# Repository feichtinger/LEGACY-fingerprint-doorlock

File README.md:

# Fingerprint Doorlock
## Overview
A simple electronic doorlock using a fingerprint sensor. 

This project uses a ZFM-20 series fingerprint sensor to implement access controll (to a building or room) using an electrical doorlock (e.g. magnetic door buzzer).

All fingerprints can be managed by a simple GUI called Fingerprint-Manager or simply over a serial terminal.

## Features
* easy access without a key, card or code (cannot be lost or forgotten)
* up to 1000 fingers can be enrolled
* whole day access option (keep the door open during events etc.)
* easy administration using the Fingerprint-Manager
* logfiles about every access (optional)

## Bill of materials
* EVK1101 Eval-Board from Atmel (a different board with an AVR32 controller might work as well)
* a ZFM-20 series fingerprint sensor e.g.
[from ebay](http://www.ebay.at/itm/Optical-Finger-print-Reader-Fingerprint-Sensor-Module-for-Arduino-Locks-/121298397934?pt=UK_BOI_Industrial_Automation_Control_ET&hash=item1c3df2aaee)
* magnetic door buzzer (I took this one [from Reichelt](http://www.reichelt.de/T-R-FFNER-1B/3/index.html?&ACTION=3&LA=446&ARTICLE=58353&artnr=T%C3%9CR%C3%96FFNER+1B&SEARCH=T%C3%83%C2%BCr%C3%83%C2%B6ffner+1B))
* power supply 9VDC, 1.5A (e.g. [from Reichelt](http://www.reichelt.de/Festspannungsnetzteile/SNT-2250-9V/3/index.html?&ACTION=3&LA=2&ARTICLE=111183&GROUPID=4946&artnr=SNT+2250+9V))
* a SD-card for the EVK1101 (capacity does not matter)
* a distribution box for the controller board
* some installation material (cables, cable channel, screws ...)
* some electronic parts from the junk box (transistor, diode, resistor, veroboard,...)

optional:

* a realtime clock module (for logfiles)
* a weather-proof button (for whole day access)

## System Components
### Fingerprintsensor
The ZFM sensor is placed in a custom housing which can easily be produced using an 3D printer (and a little bit of manual work). The housing also includes a red and a green LED and optionally a button for whole day access (see below).

The sensor should be placed on the outside next to the door and is connected to the controller board with a 7-pole cable (you can use a piece of ethernet cable for this).

### Controller Board
The controller consists of the EVK1101 and some additional electronics:

* a little PWM step down circuit (transistor + diode) to drive the buzzer
* connectors for fingerprintsensor and buzzer
* a USB to serial converter

Of course the controller board needs to be placed **behind** the door in a closed housing (you can use an distribution box for this).

The 9V power supply is directly connected to the EVK1101. Be carefull to choose a power supply that privides enough current for the buzzer. This might also be temperature dependent so better measure the buzzer current at 9V and choose a bigger power supply to be on the save side. 1.5A fits for my buzzer.

### Magnetic Door Buzzer
The buzzer only releases the falling latch, so the lock bar always has to be pulled back.

The buzzer might get warm when it is activated for a longer period of time (especially when using the whole day access). The firmware tries to reduce the power dissipation of the buzzer by reducing the holding current to 50% of starting current. Be shure that these settings work for your buzzer. (The buzzer has to open savely but must not get too hot.)

The buzzer is driven by the controller board. Ensure that the connecting cable is not accessible from the outside. If someone gets access to this cable he could easily open the door!

### PC
The normal operation (entering the door) is managed with with the above components only. But for enrolling new fingers, deleting fingers or to change settings a PC is necessary. You can either use a simple serial terminal software (e.g. cutecom) or you can use the Fingerprint-Manager.

### Realtime clock
I used the MCP7940N, a realtime clock made for 32.768kHz tuning forks with battery backup (thanks to Pointhi). I made a small PCB for the chip and its components with KiCad. It can be plugged directly into the TWI (=I²C) interface on the EVK1101.
Using the realtime clock it is possible to write log files on the SD card as it keeps the time also while the power is down or after resetting the system. This also helps at debugging.

## Netlist
There is no explicit schematic for the whole circuit but there is kind of a netlist ("netlist.ods") so you know which cable to connect to which pin. There are some slightly but necessary modifications on the EVK1101, don't forget about them!

## Software
### preparing the AVR32 toolchain
You need a bunch of software to compile the firmware for the EVK1101 and load it on the controller. This is called the toolchain. I will describe how to install the toolchain for Linux (in my case Ubuntu 14.04), if you are using windows it might be enough to install the AVR32-Studio (or maybe not), if you like to use a Mac, go somewhere else!

Create a folder on your disk for the toolchain anywhere you want, I will call it '~/AVR32_toolchain/'.

First of all we need the compiler, so go to the [Atmel-Website](http://www.atmel.com/tools/ATMELAVRTOOLCHAINFORLINUX.aspx) and download the "Atmel AVR 32-bit Toolchain 3.4.2 - Linux 64-bit" if your OS is 64-Bit. Unpack it into '~/AVR32_toolchain/'. The folder should be called "avr32-gnu-toolchain-linux_x86_64/".

Next we need the header files, so go back and download the "Atmel AVR 8-bit and 32-bit Toolchain (3.4.2) 6.1.3.1475 - Header Files". Unpack it into '~/AVR32_toolchain/' and remove the version from the folder name so the folder is called "atmel-headers/".

We also need the so called software framework so go [here](http://www.atmel.com/tools/avrsoftwareframework.aspx?tab=overview), download an unpack to '~/AVR32_toolchain/' and remove the version so the folder is called "asf/".

We are nearly finished, the last thing we need as a little programm to download the firmware to the controller, this is called dfu-programmer. Download from [Github](https://github.com/dfu-programmer/dfu-programmer), unpack in '~/AVR32_toolchain/' and rename the folder to "dfu-programmer/".

We need to compile this one so open a terminal in the folder and enter:

```
./bootstrap.sh
./configure
make
```
dfu-programmer needs access to the USB port, to enable this you have to copy the file "avr32_dfu.rules" to "/etc/udev/rules.d/". Also you have to join the group "plugdev":
`sudo usermod -aG plugdev username`  (replace 'username' by your username)

### build the firmware
To build the firmware you first have to tell the makefile where to find the toolchain, so open the makefile and edit the `TOOLCHAIN` makro (line 20) to your toolchain path.

Then call `make` to build the firmware.

Annoyingly Atmel seams to change the structure of their software framework a little bit in each revision so it might be possible that you need to change the makefile to get the firmware to build without errors.

To download the firmware you have to connect the USB-cable to the EVK1101 and turn it on. Then you have to switch the controller into bootloader mode. To do so, hold the joystick button on the EVK1101 pushed down and then press the reset button. (Now you should see a device typically called /dev/ttyACM0 in your Linux filesystem.)

To download the firmware finally call `make flash`.

Now you can connect a serial cable to the controller (baudrate 115200) and open a serial terminal (e.g. cutecom). When you press the reset button you should see a message from the firmware.

### prepare the SD card
The SD card is used to store the fingerprint database and the logfiles. The capacity of the SD-card does not realy matter, so just pick one from an old digicam for example. 

Format the SD card with FAT32. Create a file "users.txt" and a folder "logfiles".

### build the Fingerprint-Manager
The Fingerprint-Manager is a simple GUI written in Qt-5 that allows you to easily enroll and manage fingerprints. To build the Fingerprint-Manager you need to install Qt-Creator.

`sudo apt-get install qt-creator`

You also need the serial port module for Qt-5

`sudo apt-get install libqt5serialport5-dev`

Now you can simply open the Qt project (Fingerprint-Manager.pro) with Qt-Creator and build it.

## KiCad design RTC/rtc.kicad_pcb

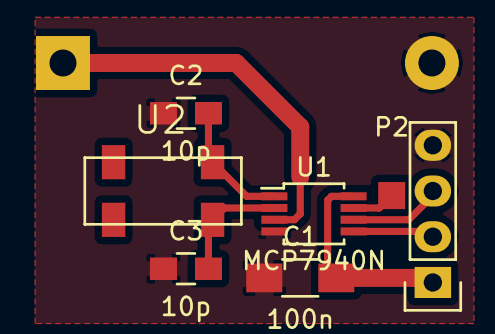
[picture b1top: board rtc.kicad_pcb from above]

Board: 2 copper layers, 8 parts (1 on the bottom side), 8 nets.

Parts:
BT1: BATTERY; keystone_103
C1: 100n; C_1206_HandSoldering
C2, C3: 10p; C_0805_HandSoldering
P1: CONN_01X04; Pin_Header_Straight_1x04
P2: CONN_01X01; Measurement_Point_Square-SMD-Pad_Small
U1: MCP7940N; MSOP-8_3x3mm_Pitch0.65mm
U2: 32.768kHz; FOX-tuning-fork

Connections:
+3V3: C1.2, P1.1, U1.8
GND: BT1.2, C1.1, C2.1, C3.1, P1.4, U1.4
unnamed: BT1.1, U1.3
unnamed: C2.2, U1.1, U2.4
unnamed: C3.2, U1.2, U2.1
unnamed: P1.2, U1.5
unnamed: P1.3, U1.6
unnamed: P2.1, U1.7

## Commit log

2015-01-27 First Commit!
2015-02-01 Fingerprint-Manager: first useable version
2015-02-04 fixed some bugs in Fingerprint-Manager
2015-02-13 added documentation
2015-02-21 [fix] bufferoverflow bug
2015-02-21 doku changed
2015-02-23 layout changed
2015-03-14 removed DCF-module
2015-03-15 some bugs at rtc fixed
2015-04-01 added brown out detection
